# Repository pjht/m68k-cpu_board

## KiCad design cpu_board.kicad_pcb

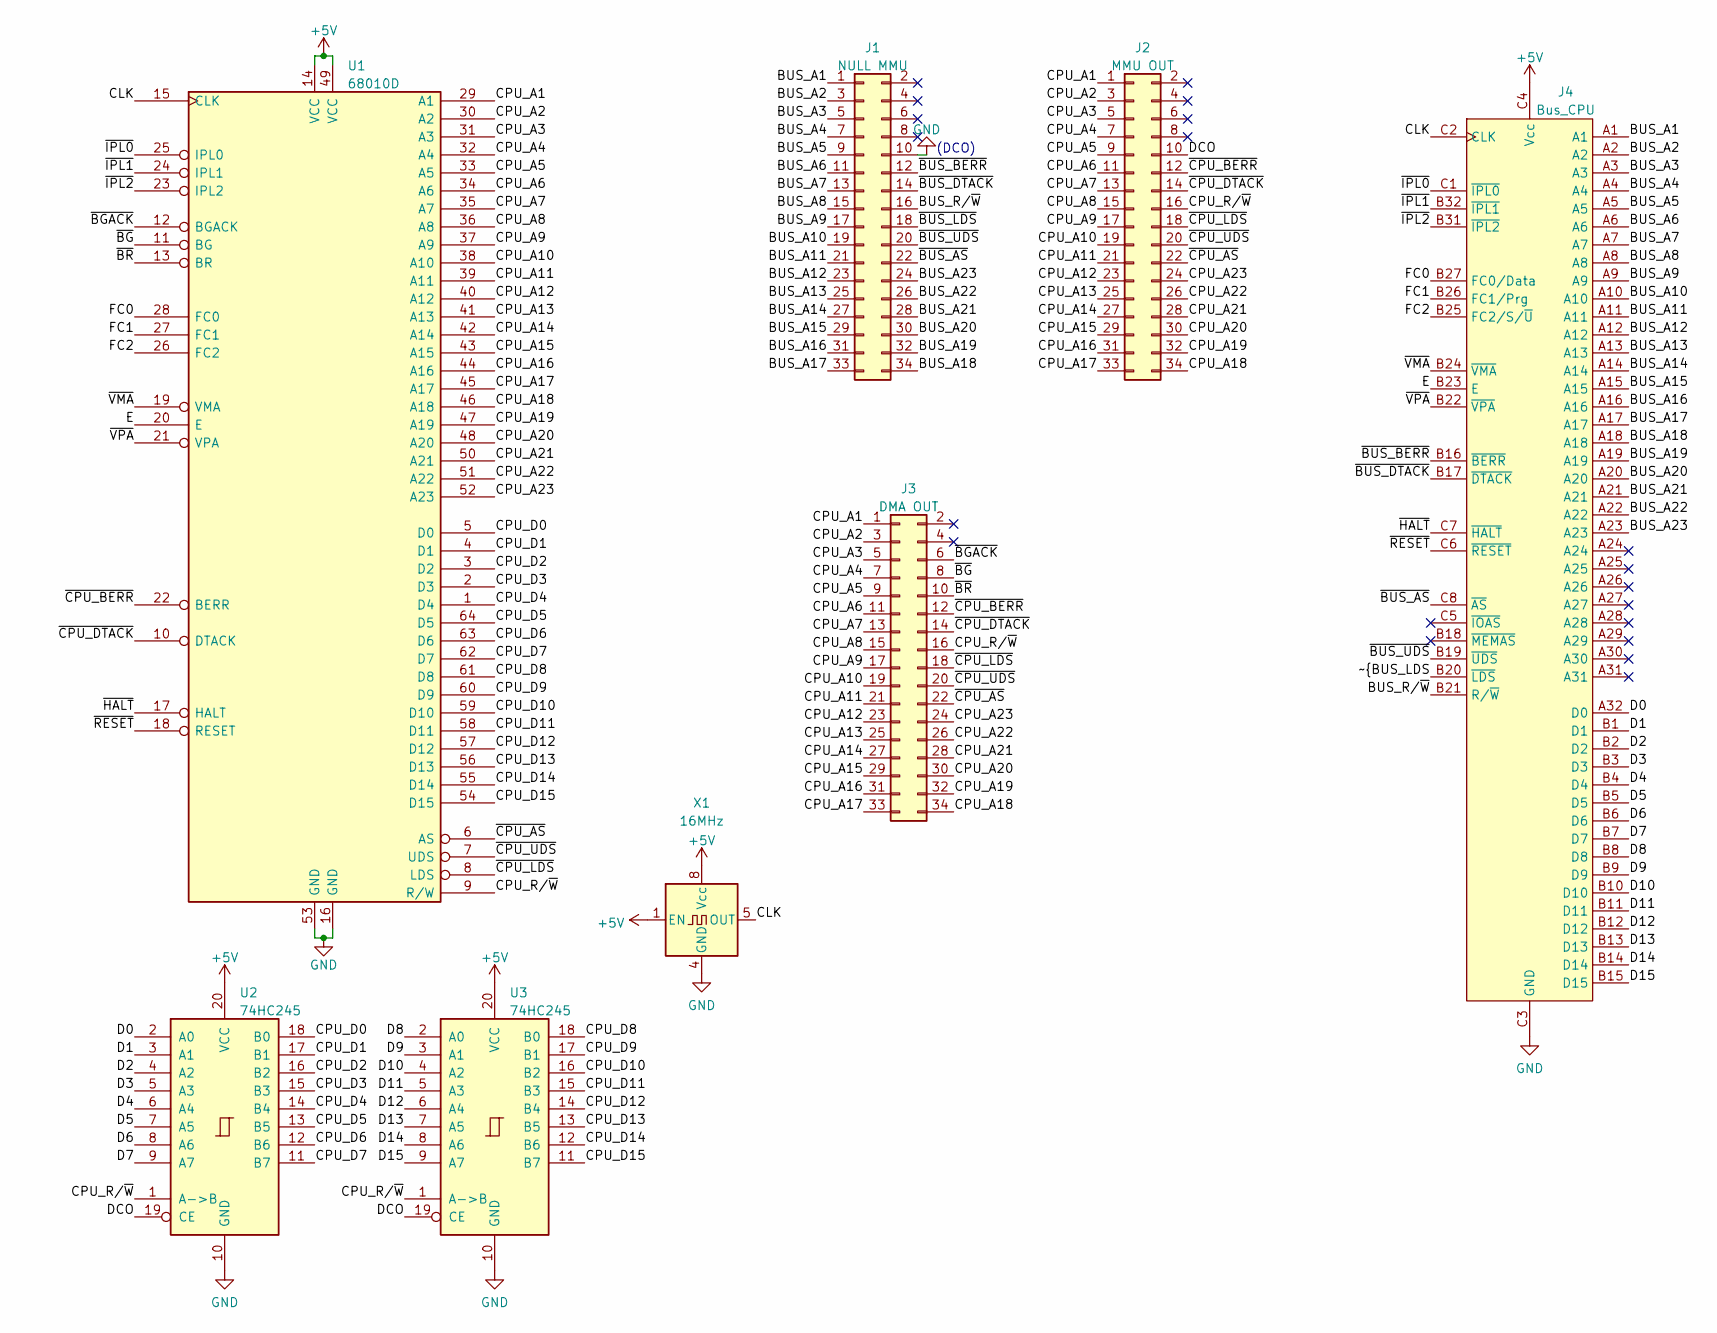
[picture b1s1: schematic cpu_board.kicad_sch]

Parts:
J1: NULL MMU; IDC-Header_2x17_P2.54mm_Vertical
J2: MMU OUT; IDC-Header_2x17_P2.54mm_Vertical
J3: DMA OUT; IDC-Header_2x17_P2.54mm_Vertical
J4: Bus_CPU; TE_536366-6
U1: 68010D; DIP-64_W25.4mm_Socket
U2, U3: 74HC245; TSSOP-20_4.4x6.5mm_P0.65mm
X1: 16MHz; Oscillator_DIP-8

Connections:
+5V: J4.C4 (Vcc), U1.14 (VCC), U1.49 (VCC), U2.20 (VCC), U3.20 (VCC), X1.1 (EN), X1.8 (Vcc)
/BUS_A1: J1.1, J4.A1
/BUS_A2: J1.3, J4.A2
/BUS_A3: J1.5, J4.A3
/BUS_A4: J1.7, J4.A4
/BUS_A5: J1.9, J4.A5
/BUS_A6: J1.11, J4.A6
/BUS_A7: J1.13, J4.A7
/BUS_A8: J1.15, J4.A8
/BUS_A9: J1.17, J4.A9
/BUS_A10: J1.19, J4.A10
/BUS_A11: J1.21, J4.A11
/BUS_A12: J1.23, J4.A12
/BUS_A13: J1.25, J4.A13
/BUS_A14: J1.27, J4.A14
/BUS_A15: J1.29, J4.A15
/BUS_A16: J1.31, J4.A16
/BUS_A17: J1.33, J4.A17
/BUS_A18: J1.34, J4.A18
/BUS_A19: J1.32, J4.A19
/BUS_A20: J1.30, J4.A20
/BUS_A21: J1.28, J4.A21
/BUS_A22: J1.26, J4.A22
/BUS_A23: J1.24, J4.A23
/BUS_R/~W: J1.16, J4.B21 (R/~W)
/CLK: J4.C2 (CLK), U1.15 (CLK), X1.5 (OUT)
/CPU_A1: J2.1, J3.1, U1.29 (A1)
/CPU_A2: J2.3, J3.3, U1.30 (A2)
/CPU_A3: J2.5, J3.5, U1.31 (A3)
/CPU_A4: J2.7, J3.7, U1.32 (A4)
/CPU_A5: J2.9, J3.9, U1.33 (A5)
/CPU_A6: J2.11, J3.11, U1.34 (A6)
/CPU_A7: J2.13, J3.13, U1.35 (A7)
/CPU_A8: J2.15, J3.15, U1.36 (A8)
/CPU_A9: J2.17, J3.17, U1.37 (A9)
/CPU_A10: J2.19, J3.19, U1.38 (A10)
/CPU_A11: J2.21, J3.21, U1.39 (A11)
/CPU_A12: J2.23, J3.23, U1.40 (A12)
/CPU_A13: J2.25, J3.25, U1.41 (A13)
/CPU_A14: J2.27, J3.27, U1.42 (A14)
/CPU_A15: J2.29, J3.29, U1.43 (A15)
/CPU_A16: J2.31, J3.31, U1.44 (A16)
/CPU_A17: J2.33, J3.33, U1.45 (A17)
/CPU_A18: J2.34, J3.34, U1.46 (A18)
/CPU_A19: J2.32, J3.32, U1.47 (A19)
/CPU_A20: J2.30, J3.30, U1.48 (A20)
/CPU_A21: J2.28, J3.28, U1.50 (A21)
/CPU_A22: J2.26, J3.26, U1.51 (A22)
/CPU_A23: J2.24, J3.24, U1.52 (A23)
/CPU_D0: U1.5 (D0), U2.18 (B0)
/CPU_D1: U1.4 (D1), U2.17 (B1)
/CPU_D2: U1.3 (D2), U2.16 (B2)
/CPU_D3: U1.2 (D3), U2.15 (B3)
/CPU_D4: U1.1 (D4), U2.14 (B4)
/CPU_D5: U1.64 (D5), U2.13 (B5)
/CPU_D6: U1.63 (D6), U2.12 (B6)
/CPU_D7: U1.62 (D7), U2.11 (B7)
/CPU_D8: U1.61 (D8), U3.18 (B0)
/CPU_D9: U1.60 (D9), U3.17 (B1)
/CPU_D10: U1.59 (D10), U3.16 (B2)
/CPU_D11: U1.58 (D11), U3.15 (B3)
/CPU_D12: U1.57 (D12), U3.14 (B4)
/CPU_D13: U1.56 (D13), U3.13 (B5)
/CPU_D14: U1.55 (D14), U3.12 (B6)
/CPU_D15: U1.54 (D15), U3.11 (B7)
/CPU_R/~W: J2.16, J3.16, U1.9 (R/W), U2.1 (A->B), U3.1 (A->B)
/D0: J4.A32 (D0), U2.2 (A0)
/D1: J4.B1 (D1), U2.3 (A1)
/D2: J4.B2 (D2), U2.4 (A2)
/D3: J4.B3 (D3), U2.5 (A3)
/D4: J4.B4 (D4), U2.6 (A4)
/D5: J4.B5 (D5), U2.7 (A5)
/D6: J4.B6 (D6), U2.8 (A6)
/D7: J4.B7 (D7), U2.9 (A7)
/D8: J4.B8 (D8), U3.2 (A0)
/D9: J4.B9 (D9), U3.3 (A1)
/D10: J4.B10 (D10), U3.4 (A2)
/D11: J4.B11 (D11), U3.5 (A3)
/D12: J4.B12 (D12), U3.6 (A4)
/D13: J4.B13 (D13), U3.7 (A5)
/D14: J4.B14 (D14), U3.8 (A6)
/D15: J4.B15 (D15), U3.9 (A7)
/DCO: J2.10, U2.19 (CE), U3.19 (CE)
/E: J4.B23 (E), U1.20 (E)
/FC0: J4.B27 (FC0/Data), U1.28 (FC0)
/FC1: J4.B26 (FC1/Prg), U1.27 (FC1)
/FC2: J4.B25 (FC2/S/~U), U1.26 (FC2)
/~BGACK: J3.6, U1.12 (BGACK)
/~BG: J3.8, U1.11 (BG)
/~BR: J3.10, U1.13 (BR)
/~BUS_AS: J1.22, J4.C8 (~AS)
/~BUS_BERR: J1.12, J4.B16 (~BERR)
/~BUS_DTACK: J1.14, J4.B17 (~DTACK)
/~BUS_UDS: J1.20, J4.B19 (~UDS)
/~CPU_AS: J2.22, J3.22, U1.6 (AS)
/~CPU_BERR: J2.12, J3.12, U1.22 (BERR)
/~CPU_DTACK: J2.14, J3.14, U1.10 (DTACK)
/~CPU_LDS: J2.18, J3.18, U1.8 (LDS)
/~CPU_UDS: J2.20, J3.20, U1.7 (UDS)
/~HALT: J4.C7 (~HALT), U1.17 (HALT)
/~IPL0: J4.C1 (~IPL0), U1.25 (IPL0)
/~IPL1: J4.B32 (~IPL1), U1.24 (IPL1)
/~IPL2: J4.B31 (~IPL2), U1.23 (IPL2)
/~RESET: J4.C6 (~RESET), U1.18 (RESET)
/~VMA: J4.B24 (~VMA), U1.19 (VMA)
/~VPA: J4.B22 (~VPA), U1.21 (VPA)
GND: J1.10, J4.C3 (GND), U1.16 (GND), U1.53 (GND), U2.10 (GND), U3.10 (GND), X1.4 (GND)

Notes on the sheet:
(DCO)

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
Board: 2 copper layers, 8 parts (0 on the bottom side), 108 nets, no tracks yet.
